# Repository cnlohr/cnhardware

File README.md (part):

# hardware

My random junk repo for random things.

If you're looking for 

**NOTE** FOR PULL REQUESTS: I DO NOT ACCEPT MASS ADDS.  If you have 5-6 really awesome parts, I'll accept a pull request, but if you have say 10+ parts, I will not.  Select only the neatest.  Also, make sure JLCPCB offers the parts, if they're intended for board mounting!

## Shortcuts

* [Discussion of ferrite cores and what their recommended power is](https://www.mag-inc.com/Media/Magnetics/File-Library/Product%20Literature/Ferrite%20Literature/Ferrite-Transformer-Design-2021.pdf)
* [Another doc like the above, but with different info](https://www.mag-inc.com/getattachment/Products/Ferrite-Cores/MagneticsFerritePowerDesign2013.pdf?)
* [Discussion of building ferrite cores](https://www.st.com/resource/en/newsletter/Wurth_Design_Considerations_Munich.pdf)
* [Breakdown voltages of enameld copper wire](https://www.edaboard.com/threads/breakdown-voltage-of-enamelled-copper-wire.407275/)
* [Enameld wire datasheet](https://www.elektrisola.com/en-us/Products/Enamelled-Wire/Technical-Data)

## Small Combo Fets

|Datasheet|LCSC|Footprint|Description|Cost 150|
|--|--|--|--|--|
|[PB544JU](https://datasheet.lcsc.com/lcsc/2005181005_NIKO-Semicon-PB544JU_C532969.pdf)|[C532969](https://www.lcsc.com/product-detail/MOSFETs_NIKO-Semicon-PB544JU_C532969.html)|DFN-6-EP(3x2)|Dual N 20v, 8m, 1.2v, 1584pF|0.1376|
|[SE4625](https://datasheet.lcsc.com/lcsc/2008291435_SINO-IC-SE4625_C730094.pdf)|[C730094](https://www.lcsc.com/product-detail/MOSFETs_SINO-IC-SE4625_C730094.html)|DFN-6L-EP(2x2)|P and N, 12v, 28/57m, 1.2v, 469pF|0.0508|
|[SED5852](https://datasheet.lcsc.com/lcsc/2208251800_SINO-IC-SED5852_C238715.pdf)|[C238715](https://www.lcsc.com/product-detail/MOSFETs_SINO-IC-SED5852_C238715.html)|DFN-6-EP(2x2)|P+Schottky, 20v, 90m, 1.2v, 540pF|0.0250|
|[WPM2006](https://datasheet.lcsc.com/lcsc/1808311525_WILLSEMI-Will-Semicon-WPM2006-6-TR_C167136.pdf)|[C167136](https://www.lcsc.com/product-detail/MOSFETs_WILLSEMI-Will-Semicon-WPM2006-6-TR_C167136.html)|DFN-6L-EP(2x2)|P+Schottky, 20v, 90m, 1.2v, 480pF|0.0579|
|[YJQ2301A](https://datasheet.lcsc.com/lcsc/2206101730_Yangzhou-Yangjie-Elec-Tech-YJQ2301A_C2942370.pdf)|[C2942370](https://www.lcsc.com/product-detail/MOSFETs_Yangzhou-Yangjie-Elec-Tech-YJQ2301A_C2942370.html)|DFN-6-EP(2x2)|Dual P 20v, 60m, 1.2v, 438pF|0.0872**|
|[HSCB20D03](https://datasheet.lcsc.com/lcsc/2105241828_HUASHUO-HSCB20D03_C2828494.pdf)|[C2828494](https://www.lcsc.com/product-detail/MOSFETs_HUASHUO-HSCB20D03_C2828494.html)|DFN-6-EP(2x2)|Dual P 20v, 90m, 1.5v, 331pF|0.0927|
|[HSCB2903](https://datasheet.lcsc.com/lcsc/2110221630_HUASHUO-HSCB2903_C2903561.pdf)|[C2903561](https://www.lcsc.com/product-detail/MOSFETs_HUASHUO-HSCB2903_C2903561.html)|DFN-6L-EP(2x2)|P and N, 20v, 40m, 100m, 1.5v, 310pF|0.1273||
|[NCE30D0808J](https://datasheet.lcsc.com/lcsc/2103121415_Wuxi-NCE-Power-Semiconductor-NCE30D0808J_C2686534.pdf)|[C2686534](https://www.lcsc.com/product-detail/MOSFETs_Wuxi-NCE-Power-Semiconductor-NCE30D0808J_C2686534.html)|DFN-6-EP(2x2)|Dual N, 30v, 35m, 2.5v, 558pF|0.1729|
|[SIA517DJ-T1-GE3](https://datasheet.lcsc.com/lcsc/2108150330_JSMSEMI-SIA517DJ-T1-GE3_C2874705.pdf)|[C2874705](https://www.lcsc.com/product-detail/MOSFETs_JSMSEMI-SIA517DJ-T1-GE3_C2874705.html)|WDFN-6-EP(2x2)|P and N, 12v, 30/70m, 590pF|0.1764|
|[DMP1046UFDB-7](https://datasheet.lcsc.com/lcsc/1912111437_Diodes-Incorporated-DMP1046UFDB-7_C461048.pdf)|[C461048](https://www.lcsc.com/product-detail/MOSFETs_Diodes-Incorporated-DMP1046UFDB-7_C461048.html)|U-DFN2020-6D|Dual N, 12v, 60m, 1.3v, 915pF|0.20|

## Interesting Fets

|Datasheet|LCSC|Footprint|Description|Cost 150|
|--|--|--|--|--|
|[WNM2096-3/TR](https://datasheet.lcsc.com/lcsc/2201121500_WILLSEMI-Will-Semicon-WNM2096-3-TR_C2931326.pdf)**|[C2931326](https://www.lcsc.com/product-detail/MOSFETs_WILLSEMI-Will-Semicon-WNM2096-3-TR_C2931326.html)|DFN-3(1x0.6)|N, 20v, 400m, 1.7v, 20pF (On Order)|0.0626|
|[TPDMN26D0UFB4](https://datasheet.lcsc.com/lcsc/2108132030_TECH-PUBLIC-TPDMN26D0UFB4_C970037.pdf)|[C970037](https://www.lcsc.com/product-detail/MOSFETs_TECH-PUBLIC-TPDMN26D0UFB4_C970037.html)|DFN-3(1x0.6)|N, 20v, 500m, 1.2v, 120pF (Cheap, Basic Sevice, Tiny, Not great but good for signals)|.0242|
|[DMN3110LCP3-7](https://datasheet.lcsc.com/lcsc/1912111437_Diodes-Incorporated-DMN3110LCP3-7_C443826.pdf)|[C443826](https://www.lcsc.com/product-detail/MOSFETs_Diodes-Incorporated-DMN3110LCP3-7_C443826.html)|X2-DSN1006-3|N, 30v, 80m, 1.3v, 140pF Wicked Awesome Case|0.1775|
|[TPM2008EP3](https://datasheet.lcsc.com/lcsc/2108132030_TECH-PUBLIC-TPM2008EP3_C2682293.pdf)|[C2682293](https://www.lcsc.com/product-detail/MOSFETs_TECH-PUBLIC-TPM2008EP3_C2682293.html)|DFN1006-3L(1x0.6)|N, 20v, 130m, 1.2v, 120pF|0.0278|
|[PNM3FD20V1E](https://datasheet.lcsc.com/lcsc/2108150430_Shanghai-Prisemi-Elec-PNM3FD20V1E_C2875806.pdf)|[C2875806](https://www.lcsc.com/product-detail/MOSFETs_Shanghai-Prisemi-Elec-PNM3FD20V1E_C2875806.html)|DFN-3L(1x0.6)|N, 20v, 200m, 1.1v, 48pF|0.0256|
|[DMN2990UFA-7B](https://datasheet.lcsc.com/lcsc/1804250226_Diodes-Incorporated-DMN2990UFA-7B_C151598.pdf)|[C151598](https://www.lcsc.com/product-detail/MOSFETs_Diodes-Incorporated-DMN2990UFA-7B_C151598.html)|XFDFN-3(0.6x0.8)|N, 20v, 900m, 1.3v, 30pF|0.0544|
|[HSCB2307](https://datasheet.lcsc.com/lcsc/2010160905_HUASHUO-HSCB2307_C845602.pdf)|[C845602](https://www.lcsc.com/product-detail/MOSFETs_HUASHUO-HSCB2307_C845602.html)|DFN-6L(2x2)|P, 20v, 15m, 1v, 2100pF|0.0789|
|[G66](https://datasheet.lcsc.com/lcsc/1809251724_GOFORD-G66_C239037.pdf)|[C239037](https://www.lcsc.com/product-detail/MOSFETs_GOFORD-G66_C239037.html)|DFN-6L(2x2)|P, 16v, 45m, 1.25v, 740pF|0.0499|
|[DMP1009UFDF](https://datasheet.lcsc.com/lcsc/2003091237_Diodes-Incorporated-DMP1009UFDF-7_C493499.pdf)|[C493499](https://www.lcsc.com/product-detail/MOSFETs_Diodes-Incorporated-DMP1009UFDF-7_C493499.html)|U-DFN2020-6|P, 12v, 11m, 1.1v, 1860pF|0.4530|
|[PJM01N20KDC](https://datasheet.lcsc.com/lcsc/2203092030_PJSEMI-PJM01N20KDC_C2981470.pdf)|[C2981470](https://www.lcsc.com/product-detail/MOSFETs_PJSEMI-PJM01N20KDC_C2981470.html)|DFN-3L(1x0.6)|N, 20v, 180m, 1.3v, 56pF|0.0259|
|[AP4580](https://datasheet.lcsc.com/lcsc/2108150030_ALLPOWER-ShenZhen-Quan-Li-Semiconductor-AP4580_C2849569.pdf)|[C2849569](https://www.lcsc.com/product-detail/MOSFETs_ALLPOWER-ShenZhen-Quan-Li-Semiconductor-AP4580_C2849569.html)|SOT-23-8L|2N and 2P Full Bridge|0.0635|
|[DMC3730UFL3-7](https://datasheet.lcsc.com/lcsc/1912111437_Diodes-Incorporated-DMC3730UFL3-7_C460973.pdf)|[C460973](https://www.lcsc.com/product-detail/MOSFETs_Diodes-Incorporated-DMC3730UFL3-7_C460973.html)|X2-DFN1310-6|Complementary P- and N- 1A, 30V TTL level FETs|0.0539|

## Special FETs

|Datasheet|LCSC|Footprint|Description|Cost 150|
|--|--|--|--|--|
|[DMZ6005E](https://datasheet.lcsc.com/lcsc/2206061716_ARK-micro-DMZ6005E_C3031422.pdf)|[C3031422](https://www.lcsc.com/product-detail/MOSFETs_ARK-micro-DMZ6005E_C3031422.html)|SOT-23|Depletion Mode N-Fet (Normally on)|0.0626|

## Interesting BJTs

|Datasheet|LCSC|Footprint|Description|Cost 150|
|--|--|--|--|--|
|[2SC4226](https://datasheet.lcsc.com/lcsc/2009141834_Slkor-SLKORMICRO-Elec--2SC4226-R25_C781319.pdf)|[C781319](https://www.lcsc.com/product-detail/Bipolar-Transistors-BJT_Slkor-SLKORMICRO-Elec-2SC4226-R25_C781319.html)|SOT-323-3|4.5GHz, 20V 100mA, 100 Hfe, +16dB@433MHz|0.0269|
|[2SC4228](https://datasheet.lcsc.com/lcsc/2009141834_Slkor-SLKORMICRO-Elec--2SC4228-R45_C781327.pdf)|[C781327](https://www.lcsc.com/product-detail/Bipolar-Transistors-BJT_Slkor-SLKORMICRO-Elec-2SC4228-R45_C781327.html)|SOT-323-3|8GHz, 20V 35mA, 150 Hfe, +19dB@433MHz|0.0464|
|[2SC4901](https://datasheet.lcsc.com/lcsc/2009141834_Slkor-SLKORMICRO-Elec--2SC4901_C781326.pdf)|[C781326](https://www.lcsc.com/product-detail/Bipolar-Transistors-BJT_Slkor-SLKORMICRO-Elec-2SC4901_C781326.html)|SOT-323-3|9GHz, 11V, 150 Hfe, +21dB@433MHz|0.0508|

## Diodes

|Datasheet|LCSC|Footprint|Description|Cost 150|
|--|--|--|--|--|
|[TPLMBR01S30ST5G](https://datasheet.lcsc.com/lcsc/2108150230_TECH-PUBLIC-TPLMBR01S30ST5G_C2858725.pdf)|[C2858725](https://www.lcsc.com/product-detail/Schottky-Barrier-Diodes-SBD_TECH-PUBLIC-TPLMBR01S30ST5G_C2858725.html)|DFN0603 (0.6x0.3)|Schottky, 30v, 0.35v, 100mA|0.0231|
|[WSB5539N-2/TR](https://datasheet.lcsc.com/lcsc/1808311538_WILLSEMI-Will-Semicon-WSB5539N-2-TR_C239808.pdf)|[C239808](https://www.lcsc.com/product-detail/Schottky-Barrier-Diodes-SBD_WILLSEMI-Will-Semicon-WSB5539N-2-TR_C239808.html)|DFN1006-2L|Schottky, 40v, 0.53v, 500mA (250mV@10mA),(350mV@100mA) (20pF)|0.0569|
|[PMEG3010EJ,115](https://datasheet.lcsc.com/lcsc/1810231722_Nexperia-PMEG3010EJ-115_C255586.pdf)***|[C255586](https://www.lcsc.com/product-detail/Schottky-Barrier-Diodes-SBD_Nexperia-PMEG3010EJ-115_C255586.html)|SOD-323F|Schottky, 30v, 0.25v, 1A (210mV@10mA),(290mV@100mA) (30pF)|0.1470|
|[1N4448HLP-7](https://datasheet.lcsc.com/lcsc/1912111437_Diodes-Incorporated-1N4448HLP-7_C154874.pdf)|[C154874](https://www.lcsc.com/product-detail/Switching-Diode_Diodes-Incorporated-1N4448HLP-7_C154874.html)|DFN-2(0.6x1)|Switching, 80v, 0.8v, 300mA|0.0232|
|[PMEG3010AESBYL](https://datasheet.lcsc.com/lcsc/2004031109_Nexperia-PMEG3010AESBYL_C503409.pdf)|[C503409](https://www.lcsc.com/product-detail/Schottky-Barrier-Diodes-SBD_Nexperia-PMEG3010AESBYL_C503409.html)|DFN1006-2L|Schottky, 1A,(200mV@10mA),(280mV@100mA) (40pF) Wicked Awesome Case|0.0936|

## TVS

|Datasheet|LCSC|Footprint|Description|Cost 150|
|--|--|--|--|--|
|[USBLC6-2P6](https://datasheet.lcsc.com/lcsc/2108132230_TECH-PUBLIC-USBLC6-2P6_C2827693.pdf)|[C2827693](https://www.lcsc.com/product-detail/ESD-Protection-Devices_TECH-PUBLIC-USBLC6-2P6_C2827693.html)|SOT-666-6|USB TVS only 2 TVS channels, 5V Operating Voltage|0.0666|

## Various LiPo / LiIon Chips

|Datasheet|LCSC|Footprint|Description|Cost 150|
|--|--|--|--|--|
|[RY2200](https://datasheet.lcsc.com/lcsc/2108251630_RYCHIP-Semiconductor-Inc--RY2200_C2888102.pdf)|[C2888102](https://www.lcsc.com/product-detail/Battery-Management-ICs_RYCHIP-Semiconductor-Inc-RY2200_C2888102.html)|SOT-23|Battery Protection|0.0431|
|[LGS4056H](https://datasheet.lcsc.com/lcsc/2210111600_Legend-Si-LGS4056H_C5124109.pdf)|[C5124109](https://www.lcsc.com/product-detail/Battery-Management-ICs_Legend-Si-LGS4056H_C5124109.html)|DFN-8(2x2)|Battery Charger, 1A|0.0891|
|[XB6042J2SV-L](https://datasheet.lcsc.com/lcsc/2104081605_XySemi-XB6042J2SV-L_C2759994.pdf)|[C2759994](https://www.lcsc.com/product-detail/Battery-Management-ICs_XySemi-XB6042J2SV-L_C2759994.html)|DFN1X1x0.37-4|Battery Protection, 44mO|0.1160|
|[LP4069TQVF](https://datasheet.lcsc.com/lcsc/2108271830_LOWPOWER-LP4069TQVF_C2890382.pdf)|[C2890382](https://www.lcsc.com/product-detail/Battery-Management-ICs_LOWPOWER-LP4069TQVF_C2890382.html)|DFN-8-EP(2x2)|Battery Charger 800mA (English Datasheet)|0.2010|
|[HP4555D8-42](https://datasheet.lcsc.com/lcsc/2006301234_HYPWR-HP4555D8-42_C648897.pdf)|[C648899](https://www.lcsc.com/product-detail/Battery-Management-ICs_HYPWR-HP4555D8-44_C648899.html)|DFN-8-EP(2x2)|Battery Charger 500mA (English Datasheet)|0.1171|
|[LP28013QVF](https://datasheet.lcsc.com/lcsc/2004281204_LOWPOWER-LP28013QVF-44_C517140.pdf)|[C517140](https://www.lcsc.com/product-detail/Battery-Management-ICs_LOWPOWER-LP28013QVF-44_C517140.html)|TDFN-10-EP(3x3)|Battery Charger (English, Interesting Blocking config) WARNING: NOT 4.2V|0.1975|
|[LP5301QVF](https://datasheet.lcsc.com/lcsc/2004281203_LOWPOWER-LP5301QVF_C517041.pdf)|[C517041](https://www.lcsc.com/product-detail/Battery-Management-ICs_LOWPOWER-LP5301QVF_C517041.html)|DFN-8-EP(2x2)|Battery Charger (English, No Blocking Diode, for backflow Structure)|0.1983|
|[WS4518D-6/TR](https://datasheet.lcsc.com/lcsc/2011111834_WILLSEMI-Will-Semicon-WS4518D-6-TR_C910991.pdf)|[C910991](https://www.lcsc.com/product-detail/Battery-Management-ICs_WILLSEMI-Will-Semicon-WS4518D-6-TR_C910991.html)|DFN-8-EP(2x2)|Battery Charger (English, Willsemi, Cheap)|0.1121|
|[XB6042Q2SV-L](https://datasheet.lcsc.com/lcsc/2104081605_XySemi-XB6042Q2SV-L_C2759995.pdf)|[C2759995](https://www.lcsc.com/product-detail/Battery-Management-ICs_XySemi-XB6042Q2SV-L_C2759995.html)|DFN-4-EP(1x1)|Protection (4.2/4.25v) 44mO|0.1160|
|[SGM41562BXG/TR](https://datasheet.lcsc.com/lcsc/2302061809_SGMICRO-SGM41562BXG-TR_C5153801.pdf)|[C5153801](https://www.lcsc.com/product-detail/Battery-Management-ICs_SGMICRO-SGM41562BXG-TR_C5153801.html)|WLCSP-9-B(1.52x1.52)|Charger + Power Path for LiPo/LiIon + I2C + Power Down Options|0.4137|
|[AW32001ECSR](https://www.lcsc.com/product-detail/Battery-Management-ICs_AWINIC-Shanghai-Awinic-Tech-AW32001ECSR_C5125890.html)|[C5125890](https://www.lcsc.com/product-detail/Battery-Management-ICs_AWINIC-Shanghai-Awinic-Tech-AW32001ECSR_C5125890.html)|WLCSP-9-B(1.68x1.68)|Charger + Power Path for LiPo/LiIon + I2C + Power Down Options *Has good power off* I intend to use this.|0.2642-0.3675|

## Flash Chips

|Datasheet|LCSC|Footprint|Description|Cost 150|
|--|--|--|--|--|
|[GD25LE64ELIGR](https://datasheet.lcsc.com/lcsc/2208221030_GigaDevice-Semicon-Beijing-GD25LE64ELIGR_C2904424.pdf)|[C2904424](https://www.lcsc.com/product-detail/NOR-FLASH_GigaDevice-Semicon-Beijing-GD25LE64ELIGR_C2904424.html)|WLCSP-8 (1.35x2.75)|NOR Flash, 64Mbit, 1.65-2v, 133MHz, 4x|0.6938|
|[ZD25WQ32CEIGR](https://datasheet.lcsc.com/lcsc/2211091800_Zetta-ZD25WQ32CEIGR_C5258281.pdf)|[C5258281](https://www.lcsc.com/product-detail/NOR-FLASH_Zetta-ZD25WQ32CEIGR_C5258281.html)|USON8-LINE(2x3)|NOR Flash, 32Mbit, 1.65-3.6v, 104MHz, 4x|0.1846|
|[P25Q32H-UXH-IR](https://datasheet.lcsc.com/lcsc/1912111437_PUYA--P25Q32H-UXH-IR_C414068.pdf)|[C414068](https://www.lcsc.com/product-detail/span-style-background-color-ff0-NOR-span-span-style-background-color-ff0-FLASH-span_PUYA-P25Q32H-UXH-IR_C414068.html)|USON8-EP(2x3)|NOR Flash, 32Mbit, 2.3-3.6v, 120MHz|0.3162|
|[ZD25WQ16BUIGR](https://datasheet.lcsc.com/lcsc/2203161812_Zetta-ZD25WQ16BUIGR_C2983691.pdf)|[C2983691](https://www.lcsc.com/product-detail/NOR-FLASH_Zetta-ZD25WQ16BUIGR_C2983691.html)|USON-8(2x3)|NOR Flash, 16Mbit, 1.65-3.6v, 104MHz|0.1782|
|[ZD25WD40BUIGR](https://datasheet.lcsc.com/lcsc/2204011630_Zetta-ZD25WD40BUIGR_C2759917.pdf)|[C2759917](https://www.lcsc.com/product-detail/span-style-background-color-ff0-NOR-span-span-style-background-color-ff0-FLASH-span_Zetta-ZD25WD40BUIGR_C2759917.html)|USON-8(2x3)|NOR Flash, 4Mbit, 1.65-2.0v, 104MHz (DIO ONLY)|0.0546|
|[ZD25WD20BUIGR](https://datasheet.lcsc.com/lcsc/2106062209_Zetta-ZD25WD20BUIGR_C2759918.pdf)|[C2759918](https://www.lcsc.com/product-detail/span-style-background-color-ff0-NOR-span-span-style-background-color-ff0-FLASH-span_Zetta-ZD25WD20BUIGR_C2759918.html)|USON-8(2x3)|NOR Flash, 2Mbit, 1.65-3.6v, 104MHz (DIO ONLY)|0.0675|
|[ZD25Q80BNIGR](https://datasheet.lcsc.com/lcsc/2206131630_Zetta-ZD25Q80BNIGR_C3035284.pdf)|[C3035284](https://www.lcsc.com/product-detail/NOR-FLASH_Zetta-ZD25Q80BNIGR_C3035284.html)|USON-8(1.5x1.5)|NOR Flash, 8Mbit, 2.3-3.6v, 104MHz (QIO ok)|0.18|
|[GD25Q128ESIGR](https://datasheet.lcsc.com/lcsc/2204011730_GigaDevice-Semicon-Beijing-GD25Q128EWIG_C2986327.pdf)|[C2928891](https://www.lcsc.com/product-detail/span-style-background-color-ff0-NOR-span-span-style-background-color-ff0-FLASH-span_GigaDevice-Semicon-Beijing-GD25Q128ESIGR_C2928891.html)|SOP-8-208mil|128 Mbit (16MByte) Flash Chip|0.7588|
|[W25Q64JVXGIQ](https://datasheet.lcsc.com/lcsc/2201121830_Winbond-Elec-W25Q64JVXGIQ_C2940195.pdf)|[C2940195](https://www.lcsc.com/product-detail/NOR-FLASH_Winbond-Elec-W25Q64JVXGIQ_C2940195.html)|USON-4x4|3.0-3.6V, 64Mbit, Dual, Quad SPI|.4964|

## RAM

|Datasheet|LCSC|Footprint|Description|Cost 150|
|--|--|--|--|--|
|[VTI7064MSME](https://datasheet.lcsc.com/lcsc/1811151432_Vilsion-Tech-VTI7064MSME_C139966.pdf)|[C139966](https://www.lcsc.com/product-detail/SRAM_Vilsion-Tech-VTI7064MSME_C139966.html)|SOP-8 (4.8mm pad centers)|64-MBit PSRAM 2.7-3.3V|3.7339|

## PCI Express

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
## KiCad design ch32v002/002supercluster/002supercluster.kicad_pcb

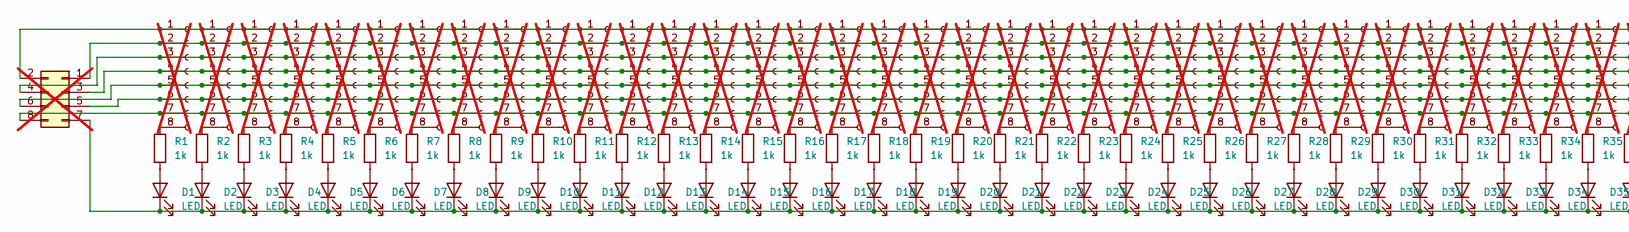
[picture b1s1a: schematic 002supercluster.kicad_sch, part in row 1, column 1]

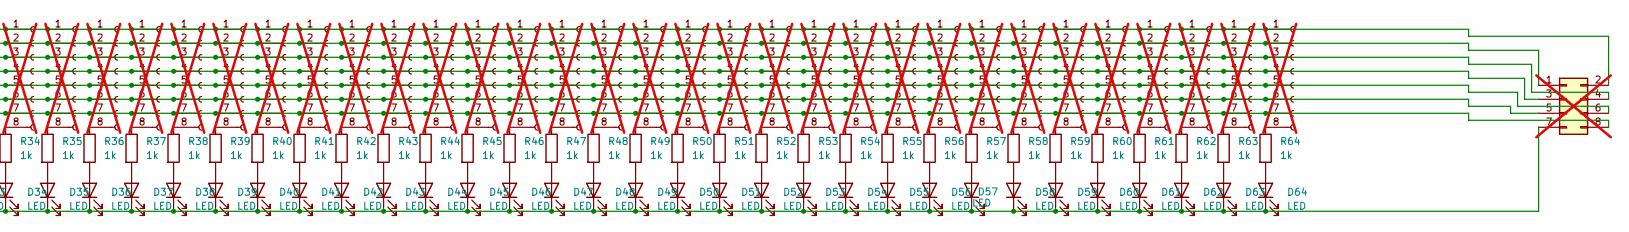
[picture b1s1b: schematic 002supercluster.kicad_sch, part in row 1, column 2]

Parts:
D1, D2, D3, D4, D5, D6, D7, D8, D9, D10, D11, D12, D13, D14, D15, D16, D17, D18, D19, D20, D21, D22, D23, D24, D25, D26, D27, D28, D29, D30, D31, D32, D33, D34, D35, D36, D37, D38, D39, D40, D41, D42, D43, D44, D45, D46, D47, D48, D49, D50, D51, D52, D53, D54, D55, D56, D57, D58, D59, D60, D61, D62, D63, D64: LED; LED_0603_1608Metric; LCSC C52675989
J1, J2, J3, J4, J5, J6, J7, J8, J10, J11, J12, J13, J14, J15, J16, J18, J19, J20, J21, J22, J23, J25, J26, J27, J28, J29, J30, J31, J32, J34, J35, J36, J37, J38, J39, J40, J41, J43, J44, J45, J46, J47, J48, J49, J51, J52, J53, J54, J55, J56, J57, J59, J60, J61, J62, J63, J64, J65, J68, J69, J70, J71, J72, J73: Conn_01x08_Socket; PinHeader_1x08_P1.27mm_Vertical; not fitted
J66, J67: Conn_02x04_Odd_Even; EDGE_02x04_2.54mm; not fitted
R1, R2, R3, R4, R5, R6, R7, R8, R9, R10, R11, R12, R13, R14, R15, R16, R17, R18, R19, R20, R21, R22, R23, R24, R25, R26, R27, R28, R29, R30, R31, R32, R33, R34, R35, R36, R37, R38, R39, R40, R41, R42, R43, R44, R45, R46, R47, R48, R49, R50, R51, R52, R53, R54, R55, R56, R57, R58, R59, R60, R61, R62, R63, R64: 1k; R_0402_1005Metric_COMPACT; LCSC C11702

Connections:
unnamed: D1.2 (A), R1.2
unnamed: D1.1 (K), D2.1 (K), D3.1 (K), D4.1 (K), D5.1 (K), D6.1 (K), D7.1 (K), D8.1 (K), D9.1 (K), D10.1 (K), D11.1 (K), D12.1 (K), D13.1 (K), D14.1 (K), D15.1 (K), D16.1 (K), D17.1 (K), D18.1 (K), D19.1 (K), D20.1 (K), D21.1 (K), D22.1 (K), D23.1 (K), D24.1 (K), D25.1 (K), D26.1 (K), D27.1 (K), D28.1 (K), D29.1 (K), D30.1 (K), D31.1 (K), D32.1 (K), D33.1 (K), D34.1 (K), D35.1 (K), D36.1 (K), D37.1 (K), D38.1 (K), D39.1 (K), D40.1 (K), D41.1 (K), D42.1 (K), D43.1 (K), D44.1 (K), D45.1 (K), D46.1 (K), D47.1 (K), D48.1 (K), D49.1 (K), D50.1 (K), D51.1 (K), D52.1 (K), D53.1 (K), D54.1 (K), D55.1 (K), D56.1 (K), D57.1 (K), D58.1 (K), D59.1 (K), D60.1 (K), D61.1 (K), D62.1 (K), D63.1 (K), D64.1 (K), J66.7, J67.7
unnamed: D2.2 (A), R2.2
unnamed: D3.2 (A), R3.2
unnamed: D4.2 (A), R4.2
unnamed: D5.2 (A), R5.2
unnamed: D6.2 (A), R6.2
unnamed: D7.2 (A), R7.2
unnamed: D8.2 (A), R8.2
unnamed: D9.2 (A), R9.2
unnamed: D10.2 (A), R10.2
unnamed: D11.2 (A), R11.2
unnamed: D12.2 (A), R12.2
unnamed: D13.2 (A), R13.2
unnamed: D14.2 (A), R14.2
unnamed: D15.2 (A), R15.2
unnamed: D16.2 (A), R16.2
unnamed: D17.2 (A), R17.2
unnamed: D18.2 (A), R18.2
unnamed: D19.2 (A), R19.2
unnamed: D20.2 (A), R20.2
unnamed: D21.2 (A), R21.2
unnamed: D22.2 (A), R22.2
unnamed: D23.2 (A), R23.2
unnamed: D24.2 (A), R24.2
unnamed: D25.2 (A), R25.2
unnamed: D26.2 (A), R26.2
unnamed: D27.2 (A), R27.2
unnamed: D28.2 (A), R28.2
unnamed: D29.2 (A), R29.2
unnamed: D30.2 (A), R30.2
unnamed: D31.2 (A), R31.2
unnamed: D32.2 (A), R32.2
unnamed: D33.2 (A), R33.2
unnamed: D34.2 (A), R34.2
unnamed: D35.2 (A), R35.2
unnamed: D36.2 (A), R36.2
unnamed: D37.2 (A), R37.2
unnamed: D38.2 (A), R38.2
unnamed: D39.2 (A), R39.2
unnamed: D40.2 (A), R40.2
unnamed: D41.2 (A), R41.2
unnamed: D42.2 (A), R42.2
unnamed: D43.2 (A), R43.2
unnamed: D44.2 (A), R44.2
unnamed: D45.2 (A), R45.2
unnamed: D46.2 (A), R46.2
unnamed: D47.2 (A), R47.2
unnamed: D48.2 (A), R48.2
unnamed: D49.2 (A), R49.2
unnamed: D50.2 (A), R50.2
unnamed: D51.2 (A), R51.2
unnamed: D52.2 (A), R52.2
unnamed: D53.2 (A), R53.2
unnamed: D54.2 (A), R54.2
unnamed: D55.2 (A), R55.2
unnamed: D56.2 (A), R56.2
unnamed: D57.2 (A), R57.2
unnamed: D58.2 (A), R58.2
unnamed: D59.2 (A), R59.2
unnamed: D60.2 (A), R60.2
unnamed: D61.2 (A), R61.2
unnamed: D62.2 (A), R62.2
unnamed: D63.2 (A), R63.2
unnamed: D64.2 (A), R64.2
unnamed: J1.1, J2.1, J3.1, J4.1, J5.1, J6.1, J7.1, J8.1, J10.1, J11.1, J12.1, J13.1, J14.1, J15.1, J16.1, J18.1, J19.1, J20.1, J21.1, J22.1, J23.1, J25.1, J26.1, J27.1, J28.1, J29.1, J30.1, J31.1, J32.1, J34.1, J35.1, J36.1, J37.1, J38.1, J39.1, J40.1, J41.1, J43.1, J44.1, J45.1, J46.1, J47.1, J48.1, J49.1, J51.1, J52.1, J53.1, J54.1, J55.1, J56.1, J57.1, J59.1, J60.1, J61.1, J62.1, J63.1, J64.1, J65.1, J66.2, J67.2, J68.1, J69.1, J70.1, J71.1, J72.1, J73.1
unnamed: J1.2, J2.2, J3.2, J4.2, J5.2, J6.2, J7.2, J8.2, J10.2, J11.2, J12.2, J13.2, J14.2, J15.2, J16.2, J18.2, J19.2, J20.2, J21.2, J22.2, J23.2, J25.2, J26.2, J27.2, J28.2, J29.2, J30.2, J31.2, J32.2, J34.2, J35.2, J36.2, J37.2, J38.2, J39.2, J40.2, J41.2, J43.2, J44.2, J45.2, J46.2, J47.2, J48.2, J49.2, J51.2, J52.2, J53.2, J54.2, J55.2, J56.2, J57.2, J59.2, J60.2, J61.2, J62.2, J63.2, J64.2, J65.2, J66.1, J67.1, J68.2, J69.2, J70.2, J71.2, J72.2, J73.2
unnamed: J1.3, J2.3, J3.3, J4.3, J5.3, J6.3, J7.3, J8.3, J10.3, J11.3, J12.3, J13.3, J14.3, J15.3, J16.3, J18.3, J19.3, J20.3, J21.3, J22.3, J23.3, J25.3, J26.3, J27.3, J28.3, J29.3, J30.3, J31.3, J32.3, J34.3, J35.3, J36.3, J37.3, J38.3, J39.3, J40.3, J41.3, J43.3, J44.3, J45.3, J46.3, J47.3, J48.3, J49.3, J51.3, J52.3, J53.3, J54.3, J55.3, J56.3, J57.3, J59.3, J60.3, J61.3, J62.3, J63.3, J64.3, J65.3, J66.4, J67.4, J68.3, J69.3, J70.3, J71.3, J72.3, J73.3
unnamed: J1.4, J2.4, J3.4, J4.4, J5.4, J6.4, J7.4, J8.4, J10.4, J11.4, J12.4, J13.4, J14.4, J15.4, J16.4, J18.4, J19.4, J20.4, J21.4, J22.4, J23.4, J25.4, J26.4, J27.4, J28.4, J29.4, J30.4, J31.4, J32.4, J34.4, J35.4, J36.4, J37.4, J38.4, J39.4, J40.4, J41.4, J43.4, J44.4, J45.4, J46.4, J47.4, J48.4, J49.4, J51.4, J52.4, J53.4, J54.4, J55.4, J56.4, J57.4, J59.4, J60.4, J61.4, J62.4, J63.4, J64.4, J65.4, J66.3, J67.3, J68.4, J69.4, J70.4, J71.4, J72.4, J73.4
unnamed: J1.5, J2.5, J3.5, J4.5, J5.5, J6.5, J7.5, J8.5, J10.5, J11.5, J12.5, J13.5, J14.5, J15.5, J16.5, J18.5, J19.5, J20.5, J21.5, J22.5, J23.5, J25.5, J26.5, J27.5, J28.5, J29.5, J30.5, J31.5, J32.5, J34.5, J35.5, J36.5, J37.5, J38.5, J39.5, J40.5, J41.5, J43.5, J44.5, J45.5, J46.5, J47.5, J48.5, J49.5, J51.5, J52.5, J53.5, J54.5, J55.5, J56.5, J57.5, J59.5, J60.5, J61.5, J62.5, J63.5, J64.5, J65.5, J66.6, J67.6, J68.5, J69.5, J70.5, J71.5, J72.5, J73.5
unnamed: J1.6, J2.6, J3.6, J4.6, J5.6, J6.6, J7.6, J8.6, J10.6, J11.6, J12.6, J13.6, J14.6, J15.6, J16.6, J18.6, J19.6, J20.6, J21.6, J22.6, J23.6, J25.6, J26.6, J27.6, J28.6, J29.6, J30.6, J31.6, J32.6, J34.6, J35.6, J36.6, J37.6, J38.6, J39.6, J40.6, J41.6, J43.6, J44.6, J45.6, J46.6, J47.6, J48.6, J49.6, J51.6, J52.6, J53.6, J54.6, J55.6, J56.6, J57.6, J59.6, J60.6, J61.6, J62.6, J63.6, J64.6, J65.6, J66.5, J67.5, J68.6, J69.6, J70.6, J71.6, J72.6, J73.6
unnamed: J1.7, J2.7, J3.7, J4.7, J5.7, J6.7, J7.7, J8.7, J10.7, J11.7, J12.7, J13.7, J14.7, J15.7, J16.7, J18.7, J19.7, J20.7, J21.7, J22.7, J23.7, J25.7, J26.7, J27.7, J28.7, J29.7, J30.7, J31.7, J32.7, J34.7, J35.7, J36.7, J37.7, J38.7, J39.7, J40.7, J41.7, J43.7, J44.7, J45.7, J46.7, J47.7, J48.7, J49.7, J51.7, J52.7, J53.7, J54.7, J55.7, J56.7, J57.7, J59.7, J60.7, J61.7, J62.7, J63.7, J64.7, J65.7, J66.8, J67.8, J68.7, J69.7, J70.7, J71.7, J72.7, J73.7
unnamed: J1.8, R1.1
unnamed: J2.8, R2.1
unnamed: J3.8, R3.1
unnamed: J4.8, R4.1
unnamed: J5.8, R5.1
unnamed: J6.8, R6.1
unnamed: J7.8, R7.1
unnamed: J8.8, R8.1
unnamed: J10.8, R9.1
unnamed: J11.8, R10.1
unnamed: J12.8, R11.1
unnamed: J13.8, R12.1
unnamed: J14.8, R13.1
unnamed: J15.8, R14.1
unnamed: J16.8, R15.1
unnamed: J18.8, R16.1
unnamed: J19.8, R17.1
unnamed: J20.8, R18.1
unnamed: J21.8, R19.1
unnamed: J22.8, R20.1
unnamed: J23.8, R21.1
unnamed: J25.8, R22.1
unnamed: J26.8, R23.1
unnamed: J27.8, R24.1
unnamed: J28.8, R25.1
unnamed: J29.8, R26.1
unnamed: J30.8, R27.1
unnamed: J31.8, R28.1
unnamed: J32.8, R29.1
unnamed: J34.8, R30.1
unnamed: J35.8, R31.1
unnamed: J36.8, R32.1
unnamed: J37.8, R33.1
unnamed: J38.8, R34.1
unnamed: J39.8, R35.1
unnamed: J40.8, R36.1
unnamed: J41.8, R37.1
unnamed: J43.8, R38.1
unnamed: J44.8, R39.1
unnamed: J45.8, R40.1
unnamed: J46.8, R41.1
unnamed: J47.8, R42.1
unnamed: J48.8, R43.1
unnamed: J49.8, R44.1
unnamed: J51.8, R45.1
unnamed: J52.8, R46.1
unnamed: J53.8, R47.1
unnamed: J54.8, R48.1
unnamed: J55.8, R49.1
unnamed: J56.8, R50.1
unnamed: J57.8, R51.1
unnamed: J59.8, R52.1
unnamed: J60.8, R53.1
unnamed: J61.8, R54.1
unnamed: J62.8, R55.1
unnamed: J63.8, R56.1
unnamed: J64.8, R57.1
unnamed: J65.8, R58.1
unnamed: J68.8, R59.1
unnamed: J69.8, R60.1
unnamed: J70.8, R61.1
unnamed: J71.8, R62.1
unnamed: J72.8, R63.1
unnamed: J73.8, R64.1

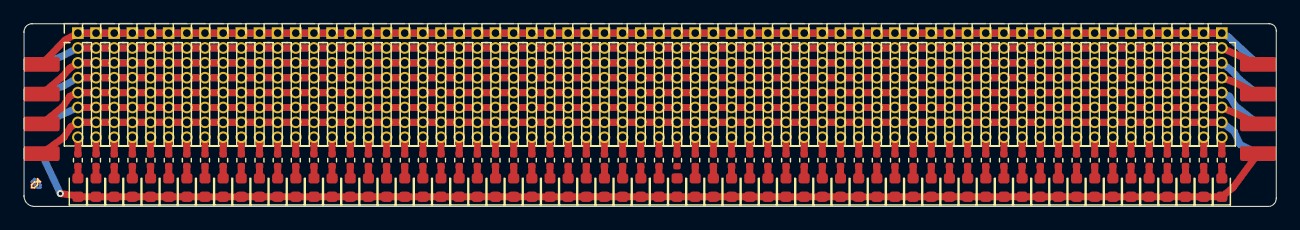
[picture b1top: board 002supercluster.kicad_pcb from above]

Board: 2 copper layers, 106.9 x 15.6 mm, 194 parts (1 on the bottom side), 136 nets.

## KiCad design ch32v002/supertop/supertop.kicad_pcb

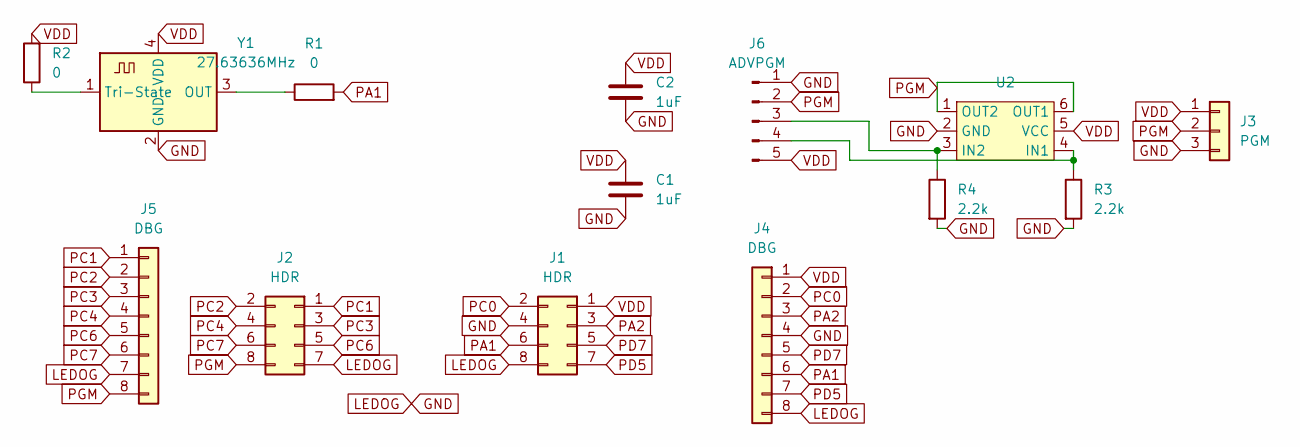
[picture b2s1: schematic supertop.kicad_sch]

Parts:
C1, C2: 1uF; C_0603_1608Metric; LCSC C15849
J1, J2: HDR; PinSocket_2x04_P2.54mm_Vertical; LCSC C55223345
J3: PGM; PinHeader_1x03_P2.54mm_Vertical; LCSC C52016391
J4, J5: DBG; PinHeader_1x08_P2.54mm_Vertical; LCSC C492407
J6: ADVPGM; PinHeader_1x05_P2.54mm_Vertical; LCSC C53055675
R1, R2: 0; R_0805_2012Metric; LCSC C17477
R3, R4: 2.2k; R_0603_1608Metric; LCSC C4190
U2: SOT-23-6; LCSC C16197225
Y1: 27.63636MHz; Crystal_SMD_SeikoEpson_TSX3225-4Pin_3.2x2.5mm; LCSC C2901579

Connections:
GND: C1.2, C2.2, J1.4, J1.8, J2.7, J3.3, J4.4, J4.8, J5.7, J6.1, R3.2, R4.2, U2.2 (GND), Y1.2 (GND); also elsewhere on the board
unnamed: J6.3, R4.1, U2.3 (IN2)
unnamed 2: J6.4, R3.1, U2.4 (IN1); also elsewhere on the board
unnamed: R1.1, Y1.3 (OUT)
unnamed: R2.1, Y1.1 (Tri-State)
PA1: J1.6, J4.6, R1.2
PA2: J1.3, J4.3
PC0: J1.2, J4.2
PC1: J2.1, J5.1
PC2: J2.2, J5.2
PC3: J2.3, J5.3
PC4: J2.4, J5.4
PC6: J2.5, J5.5
PC7: J2.6, J5.6
PD5: J1.7, J4.7
PD7: J1.5, J4.5
PGM: J2.8, J3.2, J5.8, J6.2, U2.1 (OUT2), U2.6 (OUT1)
VDD: C1.1, C2.1, J1.1, J3.1, J4.1, J6.5, R2.2, U2.5 (VCC), Y1.4 (VDD)

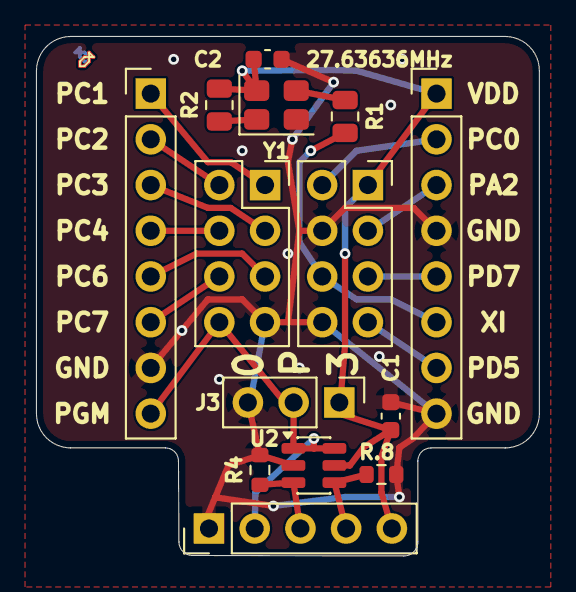
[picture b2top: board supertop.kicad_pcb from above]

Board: 2 copper layers, 27.9 x 28.9 mm, 14 parts (0 on the bottom side), 18 nets.

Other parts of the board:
R.8: 2.2k; R_0603_1608Metric

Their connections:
GND: R.8.2; also elsewhere on the board
unnamed 2: R.8.1; also elsewhere on the board

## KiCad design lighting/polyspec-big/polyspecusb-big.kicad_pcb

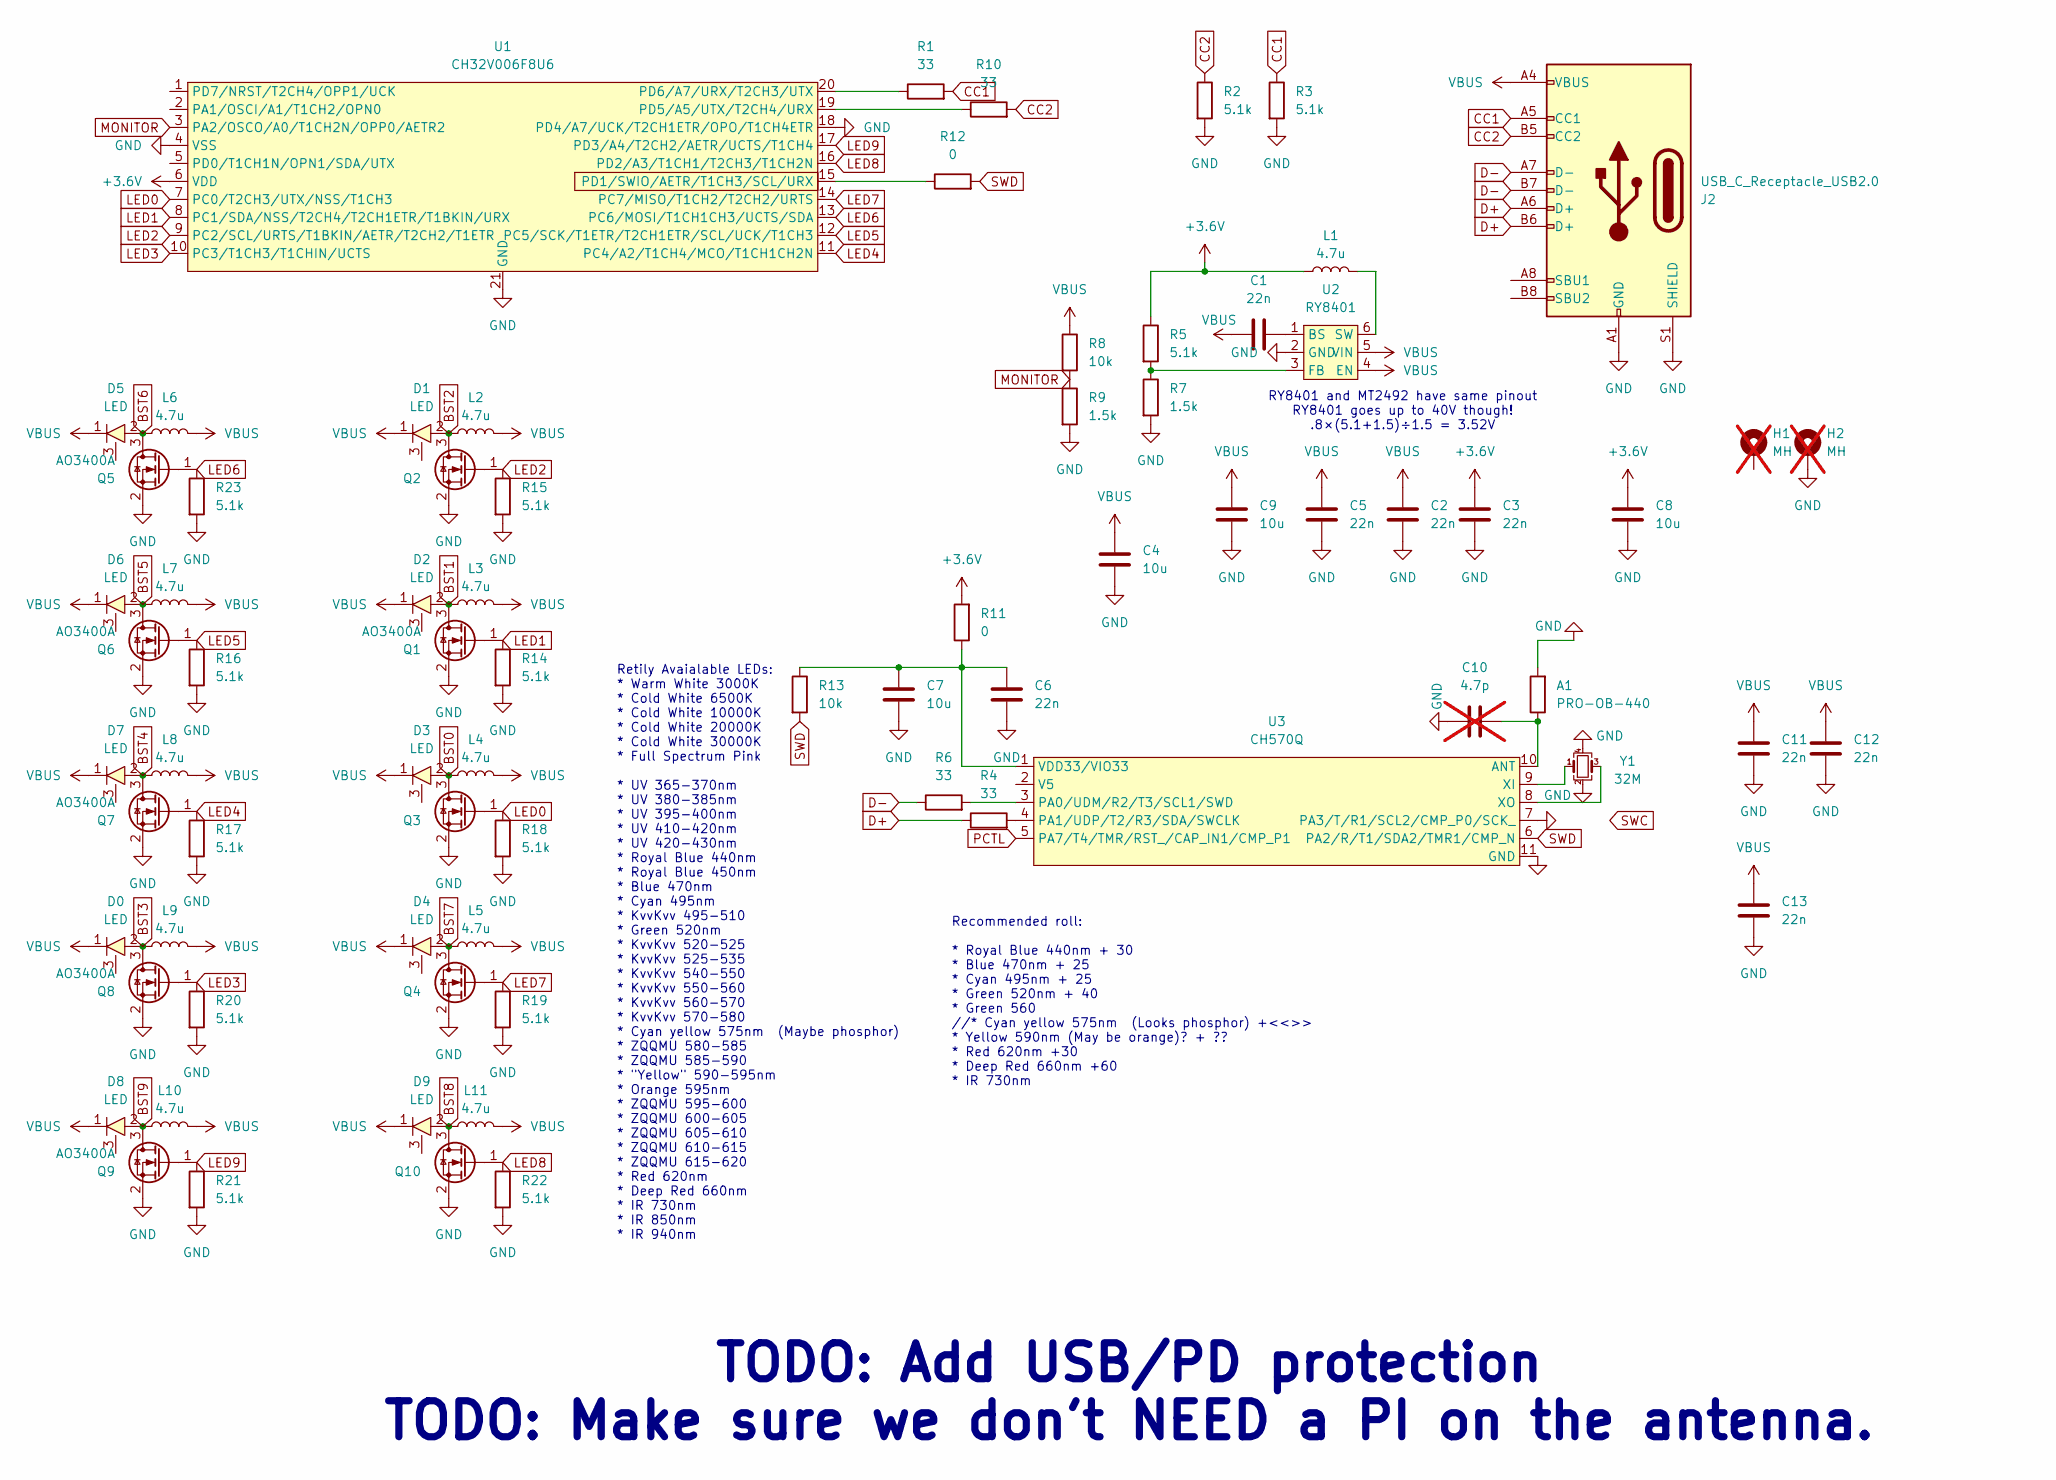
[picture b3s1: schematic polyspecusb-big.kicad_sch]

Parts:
A1: PRO-OB-440; Abracon_PRO-OB-440; LCSC C5122736
C1, C2, C3, C5, C6, C11, C12, C13: 22n; C_0402_1005Metric; LCSC C1532
C4, C7, C8, C9: 10u; C_0805_2012Metric; LCSC C15850
C10: 4.7p; C_0402_1005Metric; not fitted
D0, D1, D2, D3, D4, D5, D6, D7, D8, D9: LED; LED_3535_3W_W_PAD
H1, H2: MH; MountingHole_3.2mm_M3_ISO7380_Pad; not fitted
J2: USB_C_Receptacle_USB2.0; USB_C_SMT_ONLY_Receptacle_USB2.0; LCSC C2927040
L1, L2, L3, L4, L5, L6, L7, L8, L9, L10, L11: 4.7u; L_1008_2520Metric; LCSC C88528
Q1, Q2, Q3, Q4, Q5, Q6, Q7, Q8, Q9, Q10: AO3400A; SOT-23-EXTRASPACE; LCSC C20917
R1, R4, R6, R10: 33; R_0603_1608Metric; LCSC C23140
R2, R3, R5, R14, R15, R16, R17, R18, R19, R20, R21, R22, R23: 5.1k; R_0402_1005Metric; LCSC C25905
R7, R9: 1.5k; R_0402_1005Metric; LCSC C25867
R8, R13: 10k; R_0603_1608Metric; LCSC C25804
R11, R12: 0; R_0805_2012Metric; LCSC C17477
U1: CH32V006F8U6; QFN-20-1EP_3x3mm_P0.4mm_EP1.65x1.65mm; LCSC C42431288
U2: RY8401; SOT-23-6; LCSC C2912960
U3: CH570Q; DFN-10-1EP_3x3mm_P0.5mm_EP1.7x2.5mm; LCSC C49260680
Y1: 32M; Crystal_SMD_2016-4Pin_2.0x1.6mm; LCSC C718072

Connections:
+3.6V: C3.2, C8.2, L1.1, R5.1, R11.2, U1.6 (VDD)
BST0: D3.2, L4.1, Q3.3 (D)
BST1: D2.2, L3.1, Q1.3 (D)
BST2: D1.2, L2.1, Q2.3 (D)
BST3: D0.2, L9.1, Q8.3 (D)
BST4: D7.2, L8.1, Q7.3 (D)
BST5: D6.2, L7.1, Q6.3 (D)
BST6: D5.2, L6.1, Q5.3 (D)
BST7: D4.2, L5.1, Q4.3 (D)
BST8: D9.2, L11.1, Q10.3 (D)
BST9: D8.2, L10.1, Q9.3 (D)
CC1: J2.A5 (CC1), R1.2, R3.1
CC2: J2.B5 (CC2), R2.1, R10.2
D+: J2.A6 (D+), J2.B6 (D+), R4.1
D-: J2.A7 (D-), J2.B7 (D-), R6.1
GND: A1.2, C2.1, C3.1, C4.1, C5.1, C6.1, C7.1, C8.1, C9.1, C10.2, C11.1, C12.1, C13.1, H2.1 (1_1), J2.A1 (GND), J2.A12 (GND), J2.B1 (GND), J2.B12 (GND), J2.S1 (SHIELD), Q1.2 (S), Q2.2 (S), Q3.2 (S), Q4.2 (S), Q5.2 (S), Q6.2 (S), Q7.2 (S), Q8.2 (S), Q9.2 (S), Q10.2 (S), R2.2, R3.2, R7.2, R9.2, R14.2, R15.2, R16.2, R17.2, R18.2, R19.2, R20.2, R21.2, R22.2, R23.2, U1.4 (VSS), U1.18 (PD4/A7/UCK/T2CH1ETR/OPO/T1CH4ETR), U1.21 (GND), U2.2 (GND), U3.7 (PA3/T/R1/SCL2/CMP_P0/SCK_), U3.11 (GND), Y1.2, Y1.4
LED0: Q3.1 (G), R18.1, U1.7 (PC0/T2CH3/UTX/NSS/T1CH3)
LED1: Q1.1 (G), R14.1, U1.8 (PC1/SDA/NSS/T2CH4/T2CH1ETR/T1BKIN/URX)
LED2: Q2.1 (G), R15.1, U1.9 (PC2/SCL/URTS/T1BKIN/AETR/T2CH2/T1ETR)
LED3: Q8.1 (G), R20.1, U1.10 (PC3/T1CH3/T1CHIN/UCTS)
LED4: Q7.1 (G), R17.1, U1.11 (PC4/A2/T1CH4/MCO/T1CH1CH2N)
LED5: Q6.1 (G), R16.1, U1.12 (PC5/SCK/T1ETR/T2CH1ETR/SCL/UCK/T1CH3)
LED6: Q5.1 (G), R23.1, U1.13 (PC6/MOSI/T1CH1CH3/UCTS/SDA)
LED7: Q4.1 (G), R19.1, U1.14 (PC7/MISO/T1CH2/T2CH2/URTS)
LED8: Q10.1 (G), R22.1, U1.16 (PD2/A3/T1CH1/T2CH3/T1CH2N)
LED9: Q9.1 (G), R21.1, U1.17 (PD3/A4/T2CH2/AETR/UCTS/T1CH4)
MONITOR: R8.2, R9.1, U1.3 (PA2/OSCO/A0/T1CH2N/OPP0/AETR2)
unnamed: R12.1, U1.15 (PD1/SWIO/AETR/T1CH3/SCL/URX)
unnamed: R10.1, U1.19 (PD5/A5/UTX/T2CH4/URX)
unnamed: R1.1, U1.20 (PD6/A7/URX/T2CH3/UTX)
unnamed: C1.2, U2.1 (BS)
unnamed: R5.2, R7.1, U2.3 (FB)
unnamed: L1.2, U2.6 (SW)
unnamed: A1.1, C10.1, U3.10 (ANT)
unnamed: R6.2, U3.3 (PA0/UDM/R2/T3/SCL1/SWD)
unnamed: R4.2, U3.4 (PA1/UDP/T2/R3/SDA/SWCLK)
unnamed: C6.2, C7.2, R11.1, R13.1, U3.1 (VDD33/VIO33)
unnamed: U3.9 (XI), Y1.1
unnamed: U3.8 (XO), Y1.3
PCTL: U3.5 (PA7/T4/TMR/RST_/CAP_IN1/CMP_P1)
SWD: R12.2, R13.2, U3.6 (PA2/R/T1/SDA2/TMR1/CMP_N)
VBUS: C1.1, C2.2, C4.2, C5.2, C9.2, C11.2, C12.2, C13.2, D0.1, D1.1, D2.1, D3.1, D4.1, D5.1, D6.1, D7.1, D8.1, D9.1, J2.A4 (VBUS), J2.A9 (VBUS), J2.B4 (VBUS), J2.B9 (VBUS), L2.2, L3.2, L4.2, L5.2, L6.2, L7.2, L8.2, L9.2, L10.2, L11.2, R8.1, U2.4 (EN), U2.5 (VIN)

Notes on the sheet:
Retily Avaialable LEDs: * Warm White 3000K * Cold White 6500K * Cold White 10000K * Cold White 20000K * Cold White 30000K * Full Spectrum Pink * UV 365-370nm * UV 380-385nm * UV 395-400nm * UV 410-420nm * UV 420-430nm * Royal Blue 440nm * Royal Blue 450nm * Blue 470nm * Cyan 495nm * KvvKvv 495-510 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
Recommended roll: * Royal Blue 440nm + 30 * Blue 470nm + 25 * Cyan 495nm + 25 * Green 520nm + 40 * Green 560 //* Cyan yellow 575nm (Looks phosphor) +<<>> * Yellow 590nm (May be orange)? + ?? * Red 620nm +30 * Deep Red 660nm +60 * IR 730nm
TODO: Add USB/PD protection TODO: Make sure we don't NEED a PI on the antenna.
RY8401 and MT2492 have same pinout RY8401 goes up to 40V though! .8×(5.1+1.5)÷1.5 = 3.52V

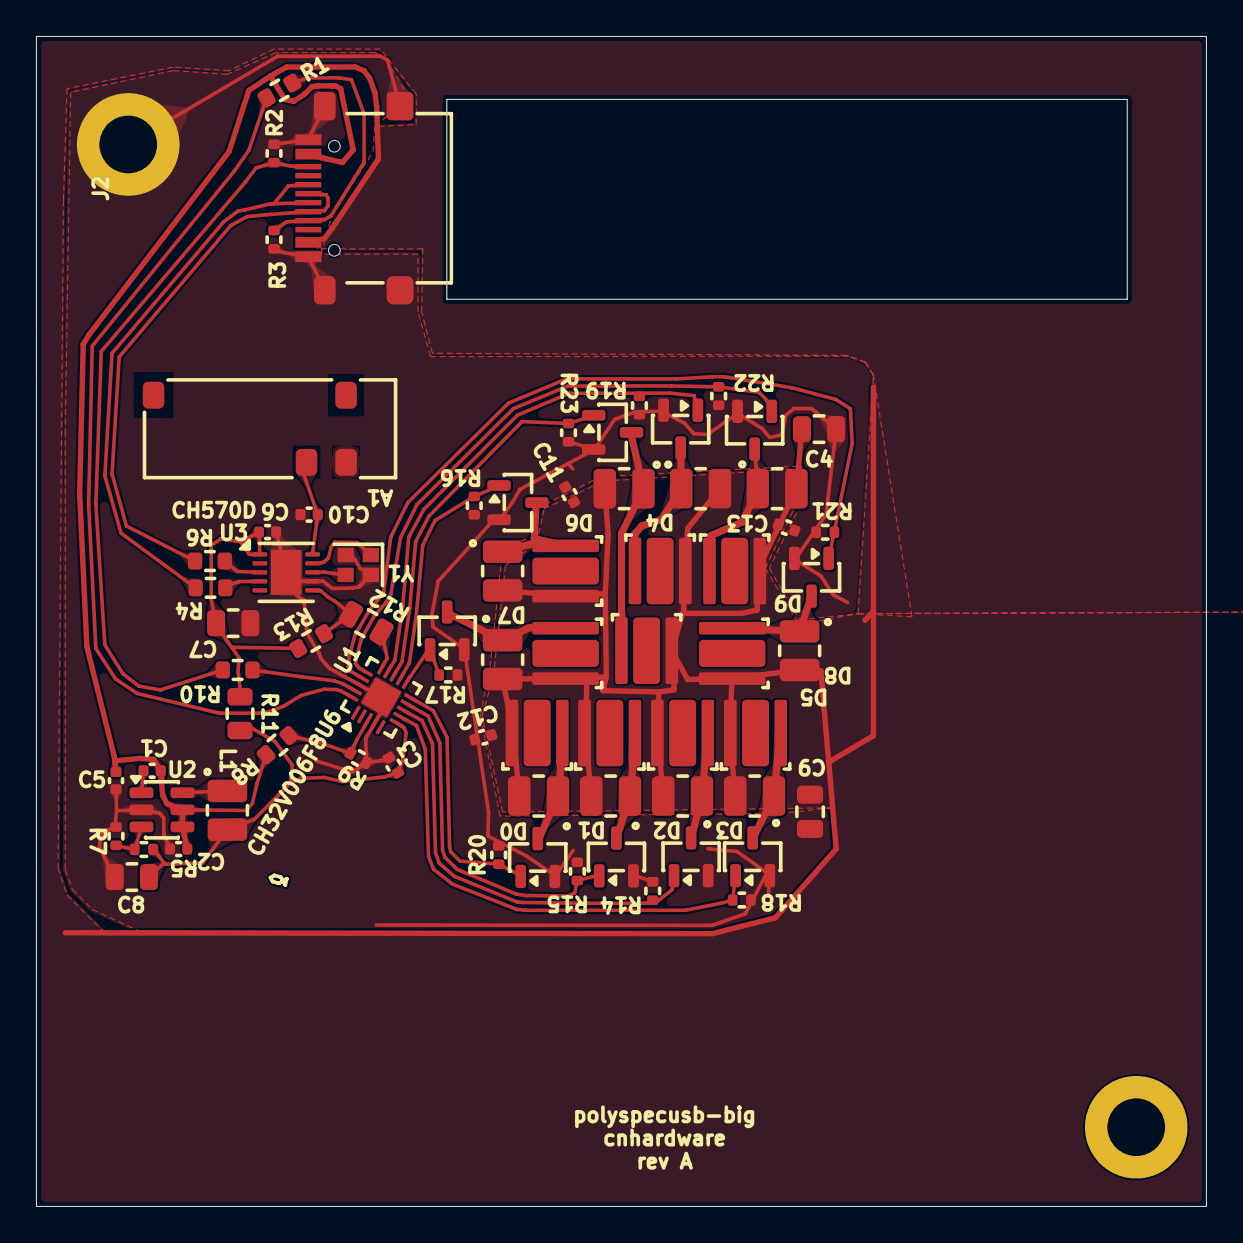
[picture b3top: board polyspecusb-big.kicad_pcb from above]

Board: 2 copper layers, 65.0 x 65.0 mm, 75 parts (0 on the bottom side), 41 nets.

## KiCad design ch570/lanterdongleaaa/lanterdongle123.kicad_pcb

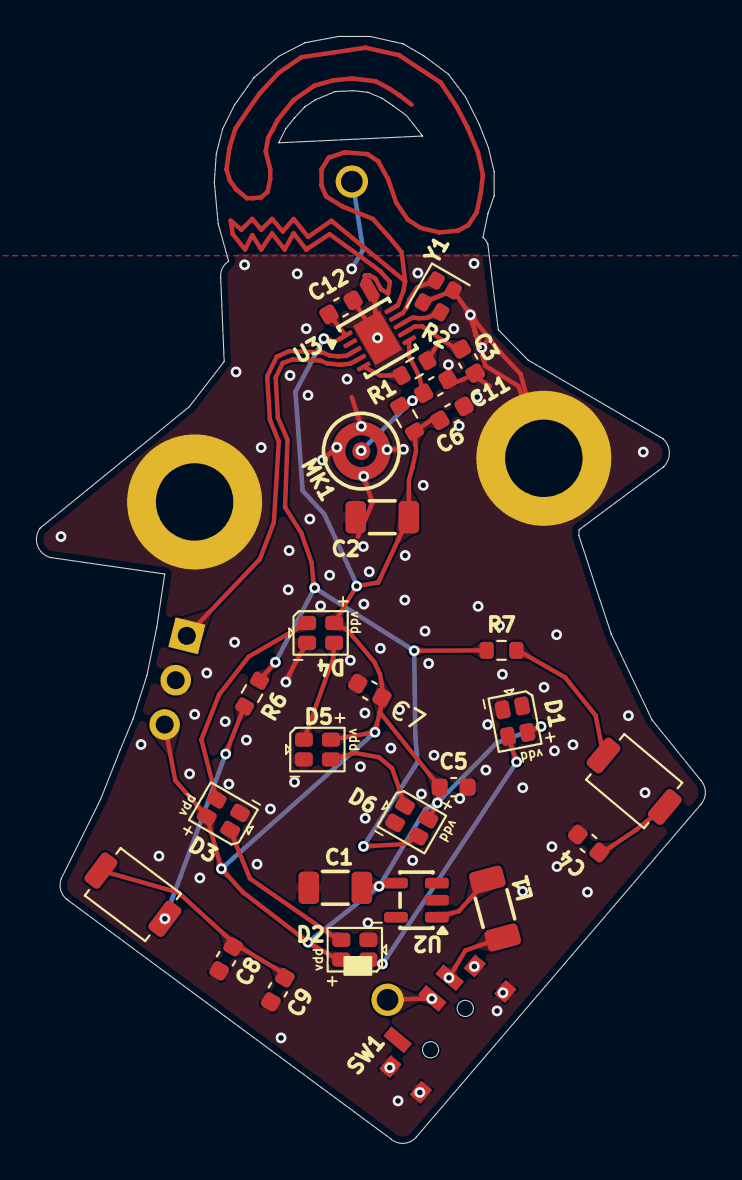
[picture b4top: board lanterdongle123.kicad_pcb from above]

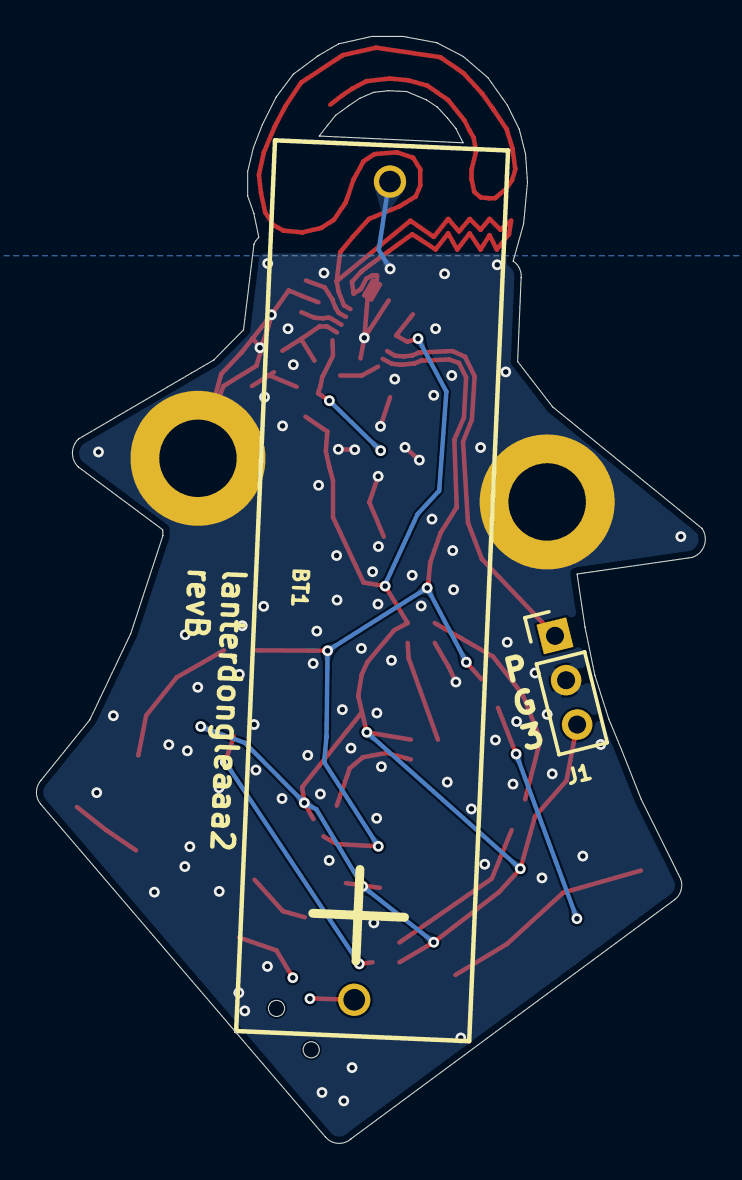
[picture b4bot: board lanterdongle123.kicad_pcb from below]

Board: 2 copper layers, 37.2 x 61.5 mm, 35 parts (2 on the bottom side), 22 nets.

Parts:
A1: toppart
BT1: Battery_Cell; BAT-TH_BH-AAA-A1AJ001
C1, C2: 22uF; C_1206_3216Metric
C3, C4, C5, C6, C7, C8, C9, C12: 33nF; C_0603_1608Metric
C11: 10nF; C_0603_1608Metric
D1, D2, D3, D4, D5, D6: WS2812C_2020_XL_0807_RGB_LED
H1, H2: MountingHole_Pad; MountingHole_4.3mm_M4_DIN965_Pad
J1: PGM; PinHeader_1x03_P2.54mm_Vertical
L1: 4.7uH; L_1206_3216Metric_Pad1.22x1.90mm_HandSolder
MK1: Microphone; CUI_CMC-4013-SMT
NT1: NetTie_2; NetTie-2_SMD_Pad0.5mm
R1, R2, R6, R7: 4.7k; R_0603_1608Metric
SW1: PWR; SW_SPDT_PCM12
SW2, SW3: SW_SPST; SW_SPST_TS-1088-xR020
U2: TPS613221ADBV; SOT-23-5
U3: CH572Q; DFN-10-1EP_3x3mm_P0.5mm_EP1.7x2.5mm
Y1: 32M; Crystal_SMD_2016-4Pin_2.0x1.6mm

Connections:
+3.3V: C1.1, C2.1, C5.1, C6.1, C7.1, C12.1, D1.2 (V+), D2.2 (V+), D3.2 (V+), D4.2 (V+), D5.2 (V+), D6.2 (V+), J1.3, R1.1, U2.4 (VOUT), U3.1 (VDD33/VIO33)
GND: BT1.2 (-), C1.2, C2.2, C3.2, C4.2, C5.2, C6.2, C7.2, C8.2, C9.2, C11.1, C12.2, D1.3 (GND), D2.3 (GND), D3.3 (GND), D4.3 (GND), D5.3 (GND), D6.3 (GND), H1.1 (1_1), H2.1 (1_1), J1.2, MK1.1 (-), NT1.2, SW1.4, SW1.5, SW1.6, SW1.7, U2.2 (GND), U3.11 (GND), Y1.2, Y1.4
LED: D6.4 (DI), R6.1, R7.1, U3.4 (PA1/UDP/T2/R3/SDA/SWCLK)
unnamed: BT1.1 (+), SW1.2
unnamed: D1.4 (DI), D2.1 (DO)
unnamed: D2.4 (DI), D3.1 (DO)
unnamed: D3.4 (DI), D4.1 (DO)
unnamed: D4.4 (DI), D5.1 (DO)
unnamed: D5.4 (DI), D6.1 (DO)
unnamed: L1.1, SW1.3
unnamed: R7.2, SW2.1 (A)
unnamed: C4.1, SW2.2 (B)
unnamed: R6.2, SW3.1 (A)
unnamed: C8.1, C9.1, SW3.2 (B)
unnamed: L1.2, U2.1 (SW)
unnamed: NT1.1, U3.10 (ANT)
unnamed: U3.9 (XI), Y1.1
unnamed: U3.8 (XO), Y1.3
PA2: C11.2, MK1.2 (+), R1.2, U3.6 (PA2/R/T1/SDA2/TMR1/CMP_N)
PA3: C3.1, R2.2, U3.7 (PA3/T/R1/SCL2/CMP_P0/SCK_)
PWM: R2.1, U3.5 (PA7/T4/TMR/RST_/CAP_IN1/CMP_P1)
SWD: J1.1, U3.3 (PA0/UDM/R2/T3/SCL1/SWD)
